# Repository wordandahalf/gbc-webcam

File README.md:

### gbc-webcam
A color webcam made using the M64282FP silicon retina found in the Gameboy Camera. Using a trichroic prism salvaged from a Hitachi HV-C20 3CCD camera, three M64282FP sensors are combined with an STM32H755 Nucleo development board to create a fully functional USB webcam.

##### Structure
- `adapters/` contains the FreeCAD files for the shims to adapt the prism mounting system to the sensors.
- `analysis/` contains Typst source files to generate a report regarding the analysis of the silicon retnia.
- `calibration/` contains Python source files to perform the necessary color calibration of the three sensors.
- `firmware/` contains the STM32CubeIDE project for programming the STM32H755 development board with the USB webcam firmware.

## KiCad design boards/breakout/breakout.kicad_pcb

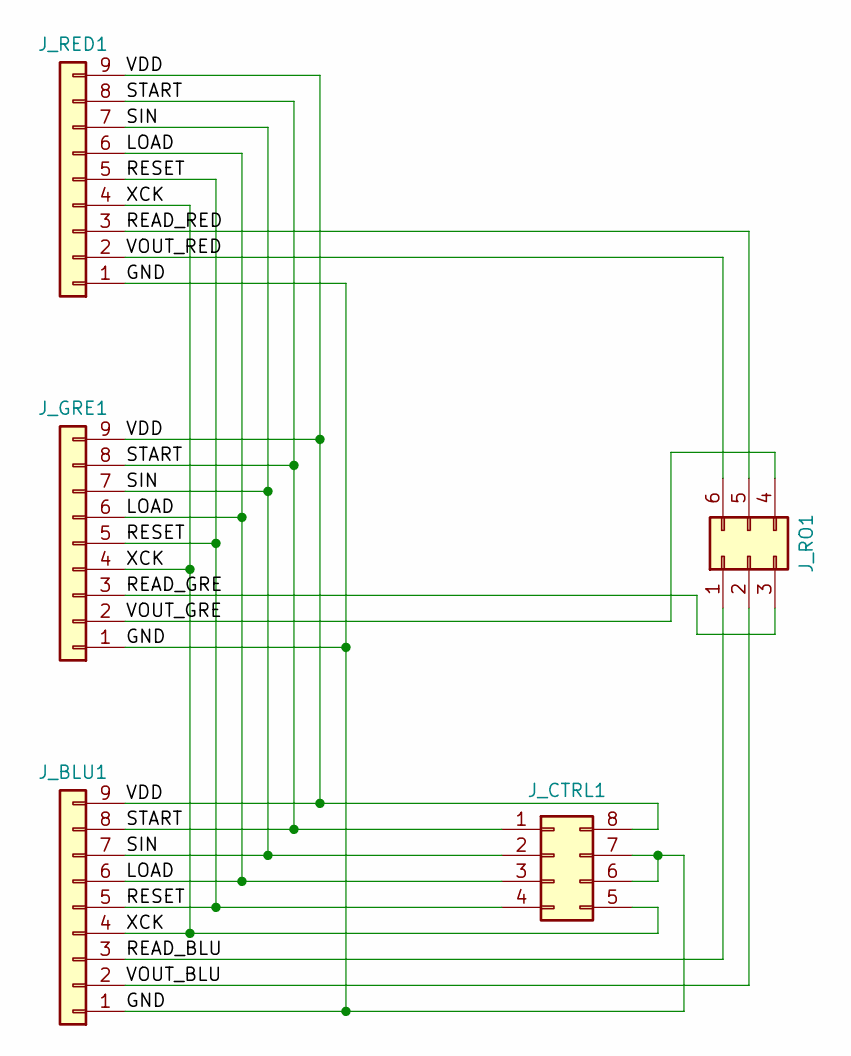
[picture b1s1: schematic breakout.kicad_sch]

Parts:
J_BLU1: Conn_01x09; JST_ZH_B9B-ZR_1x09_P1.50mm_Vertical
J_CTRL1: Conn_02x04_Counter_Clockwise; PinSocket_2x04_P2.54mm_Horizontal
J_GRE1: Conn_01x09; JST_ZH_B9B-ZR_1x09_P1.50mm_Vertical
J_RED1: Conn_01x09; JST_ZH_B9B-ZR_1x09_P1.50mm_Vertical
J_RO1: Conn_02x03_Counter_Clockwise; PinSocket_2x03_P2.54mm_Horizontal

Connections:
/GND: J_BLU1.1, J_CTRL1.6, J_CTRL1.7, J_GRE1.1, J_RED1.1
/LOAD: J_BLU1.6, J_CTRL1.3, J_GRE1.6, J_RED1.6
/READ_BLU: J_BLU1.3, J_RO1.1
/READ_GRE: J_GRE1.3, J_RO1.3
/READ_RED: J_RED1.3, J_RO1.5
/RESET: J_BLU1.5, J_CTRL1.4, J_GRE1.5, J_RED1.5
/SIN: J_BLU1.7, J_CTRL1.2, J_GRE1.7, J_RED1.7
/START: J_BLU1.8, J_CTRL1.1, J_GRE1.8, J_RED1.8
/VDD: J_BLU1.9, J_CTRL1.8, J_GRE1.9, J_RED1.9
/VOUT_BLU: J_BLU1.2, J_RO1.2
/VOUT_GRE: J_GRE1.2, J_RO1.4
/VOUT_RED: J_RED1.2, J_RO1.6
/XCK: J_BLU1.4, J_CTRL1.5, J_GRE1.4, J_RED1.4

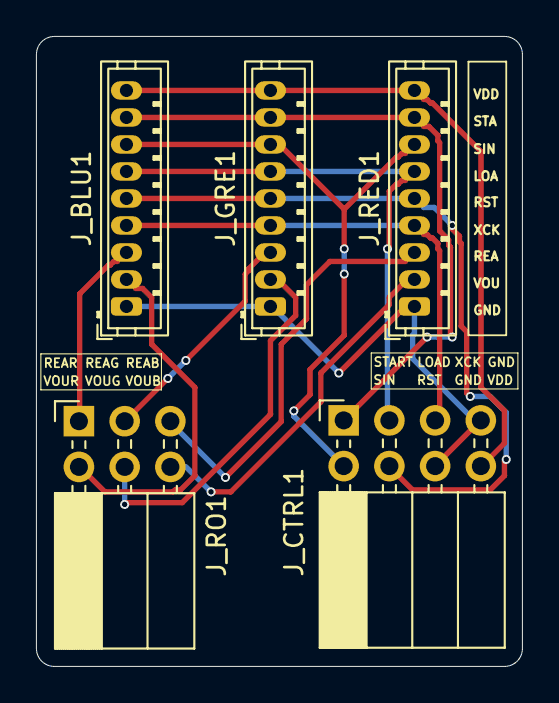
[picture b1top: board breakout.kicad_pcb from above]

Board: 2 copper layers, 27.0 x 35.0 mm, 5 parts (0 on the bottom side), 13 nets.

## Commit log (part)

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2025-09-04 add: baseline protocol implementation
2025-09-04 add: hal for sensor registers, clean up code.
2025-09-05 add: resonable default values
2025-09-06 change: parameterize project for configurable clocks
2025-09-06 fix: PIO already uses divided clocks
2025-09-07 change: fire IRQ1 for ADC sampling, fix active-low reset
2025-09-07 fix: reset pulled low, incorrect ordering of pixel sample IRQ
2025-09-07 change: simplify PIO program by using side-set more extensively, properly pack register values into FIFO
2025-09-07 add: example capture from cartridge
2025-09-09 change: prefer smaller binary sizes over speed
2025-09-11 change: working poc, had to work through inaccuracies in datasheet.
2025-09-14 add: baseline Pico SDK implementation. ADC/DMA timing needs improvement
2025-09-18 add: temporary buffer for re-synchronizing frames due to ADC DMA misalignment
2025-09-18 add: python application for streaming camera data
2025-09-18 change: update README with goal
2025-10-07 change: update README on current status
2026-01-08 fix: typo
2026-03-07 add: new STM32-based implmenetation
2026-03-07 add: utilized resources
